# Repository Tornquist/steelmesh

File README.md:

# Steelmesh
(Twitch Plays ECE477 -- Collaborative Robot Project)

This repository is set up to simulate an organization.  Instead of a seperate repository for each piece of the project, each branch represents a valid section/piece of the project.

## irc_work
The irc bot and rails webserver that manages the stream of communication from Twitch.TV and allows the robots to request commands. 

## WiFi
The final embedded robot software.

## PCB
The PCB design used for the robots

## raspberry_pi
The logic that controlled the scoring system and webcam feeds that ran the arena.

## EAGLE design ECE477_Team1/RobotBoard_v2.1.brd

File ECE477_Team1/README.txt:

1)  Install Eagle
2)  Add the Sparkfun libraries (https://learn.sparkfun.com/tutorials/how-to-install-and-setup-eagle/using-the-sparkfun-libraries)
3)  Copy the microchip.lbr file into your lbr directory (it will overwrite the current microchip library).
3.1)  Also copy the Johanson_antenna.lbr and crw.lbr files
4)  You probably have to add the project folder to the "Projects" directory list (kinda like the libraries).
5)  Open the schematic/board and look at it and stuff.
6)  ????????????
7)  Profit.

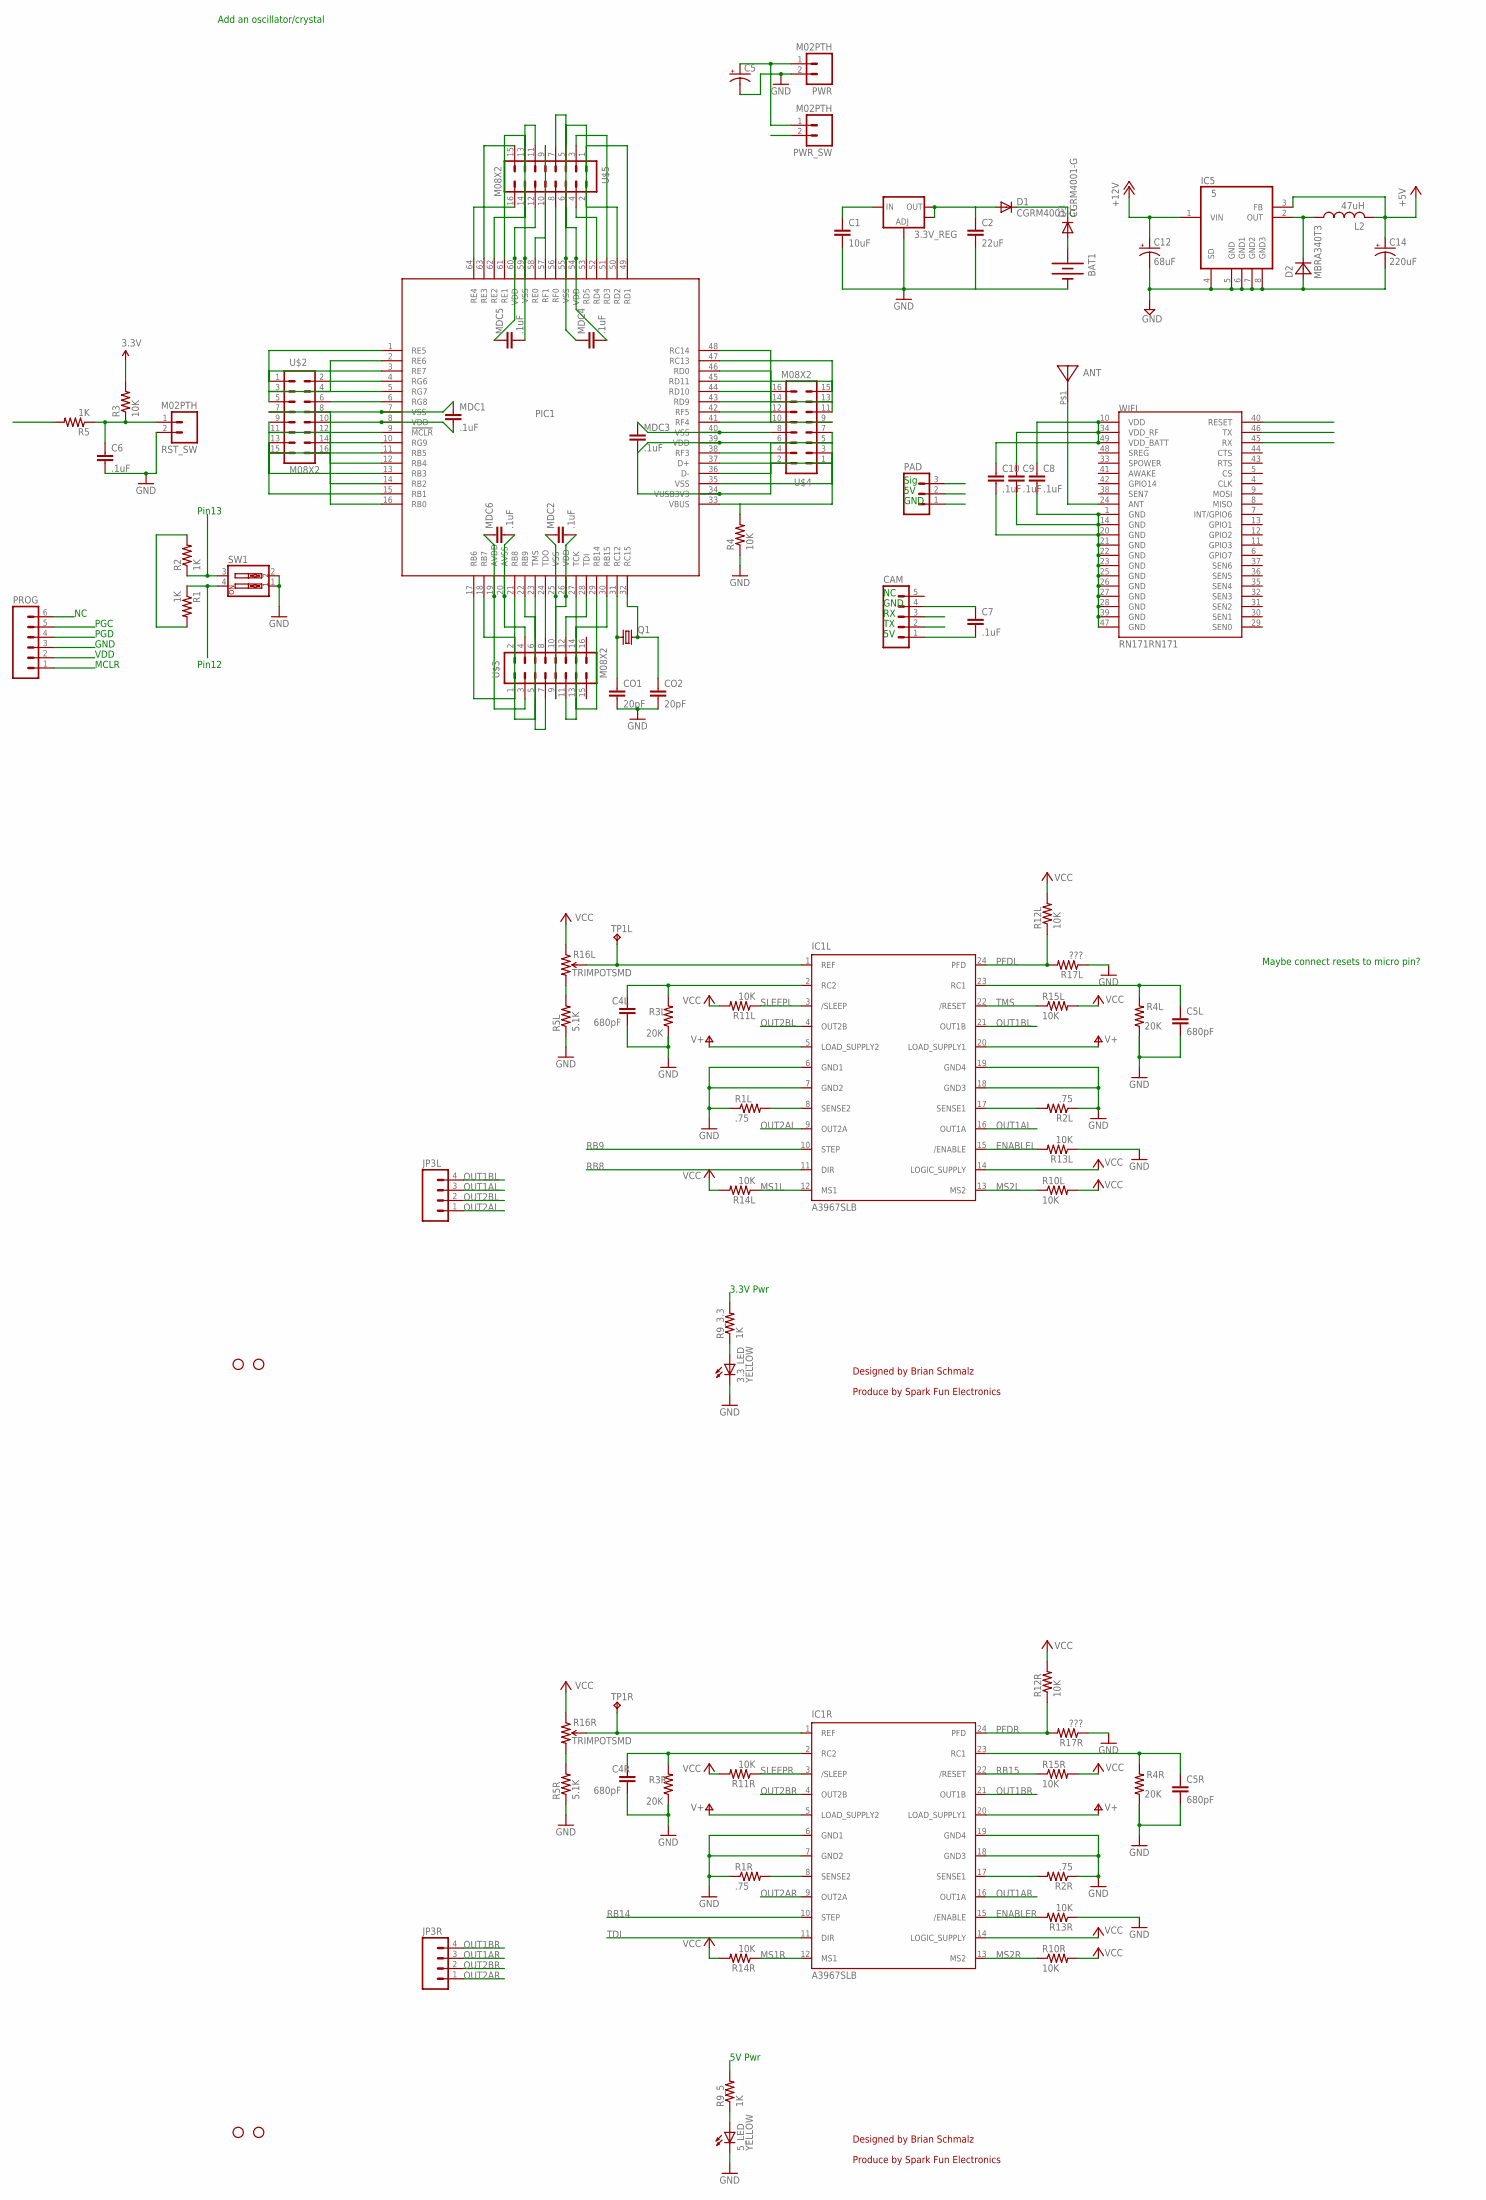
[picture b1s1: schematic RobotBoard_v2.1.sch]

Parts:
3.3V_REG: V_REG_LM1117SOT223; SOT223
3.3_LED, 5_LED: YELLOW; LED-0603
ANT: 2450AT18A100
BAT1: BATTERY20PTH; BATTCOM_20MM_PTH
C1: 10uF; 0603
C2: 22uF; 0603
C4L, C4R, C5L, C5R: 680pF; C0402
C5: CAP_POLPTH4; CPOL-RADIAL-1000UF-25V
C6, C7, C8, C9, C10: .1uF; 0603
C12: 68uF; PANASONIC_D
C14: 220uF; PANASONIC_D
CAM: M05LOCK; 1X05_LOCK
CO1, CO2: 20pF; 0603
D1, D3: CGRM4001-G; SOD-123_MINI-SMA
D2: MBRA340T3; SMA
IC1L, IC1R: A3967SLB; SO24W
IC5: 5; SO08
JP1, JP2, JP8, JP9: STAND-OFF
JP3L, JP3R: M041X04_NO_SILK; 1X04_NO_SILK
L2: 47uH; 6000-XXXX-RC
MDC1, MDC2, MDC3, MDC4, MDC5, MDC6: .1uF; 0603
PAD: M03POLAR; MOLEX-1X3
PIC1: PIC32MZ2048ECM064; TQFP64-10X10X1MM
PROG: M06LOCK; 1X06_LOCK
PWR: M02PTH; 1X02
PWR_SW: M02PTH; 1X02
Q1: CRYSTALHC49UP; HC49UP
R1, R2, R5, R9_3.3, R9_5: 1K; C0402
R1L, R1R, R2L, R2R: .75; R0805
R3, R4, R10L, R10R, R11L, R11R, R12L, R12R, R13L, R13R, R14L, R14R, R15L, R15R: 10K; C0402
R3L, R3R, R4L, R4R: 20K; C0402
R5L, R5R: 5.1K; C0402
R16L, R16R: TRIMPOTSMD; TRIMPOT-3MM
R17L, R17R: ???; C0402
RST_SW: M02PTH; 1X02
SW1: SW_DIP-2; DIPSWITCH-02
TP1L, TP1R: TPPAD1-13; P1-13
U$2, U$3, U$4, U$5: M08X2; 2X8
WIFI: RN171RN171; RN171

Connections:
3.3V: C8.1, C9.1, C10.1, D1.C, D3.C, IC1L.14 (LOGIC_SUPPLY), IC1R.14 (LOGIC_SUPPLY), MDC1.2, MDC2.2, MDC3.2, MDC4.2, MDC5.1, MDC6.1, PIC1.8 (VDD), PIC1.19 (AVDD), PIC1.26 (VDD), PIC1.34 (VUSB3V3), PIC1.39 (VDD), PIC1.54 (VDD), PIC1.60 (VDD), PROG.2, R1.2, R2.2, R3.2, R9_3.3.2, R10L.2, R10R.2, R11L.2, R11R.2, R12L.2, R12R.2, R14L.2, R14R.2, R15L.2, R15R.2, R16L.1 (CCW), R16R.1 (CCW), U$2.8, U$3.3, U$3.10, U$4.2, U$4.7, U$5.6, U$5.12, WIFI.10 (VDD), WIFI.34 (VDD_RF), WIFI.49 (VDD_BATT)
5V: 3.3V_REG.3 (IN), C1.1, C7.2, C14.+, CAM.1, IC5.3 (FB), L2.2, PAD.2, R9_5.2
12V: C12.+, IC1L.5 (LOAD_SUPPLY2), IC1L.20 (LOAD_SUPPLY1), IC1R.5 (LOAD_SUPPLY2), IC1R.20 (LOAD_SUPPLY1), IC5.1 (VIN), PWR_SW.2
!MCLR: PIC1.9 (!MCLR), PROG.1, R5.2, U$2.9
A44: C6.1, R3.1, R5.1, RST_SW.1
D+: PIC1.37 (D+), U$4.5
D-: PIC1.36 (D-), U$4.4
ENABLEL: IC1L.15 (/ENABLE), R13L.2
ENABLER: IC1R.15 (/ENABLE), R13R.2
GND: 3.3V_REG.1 (ADJ), 3.3_LED.C, 5_LED.C, BAT1.2 (-), C1.2, C2.2, C4L.2, C4R.2, C5.2 (-), C5L.2, C5R.2, C6.2, C7.1, C8.2, C9.2, C10.2, C12.-, C14.-, CAM.4, CO1.2, CO2.2, D2.A, IC1L.6 (GND1), IC1L.7 (GND2), IC1L.18 (GND3), IC1L.19 (GND4), IC1R.6 (GND1), IC1R.7 (GND2), IC1R.18 (GND3), IC1R.19 (GND4), IC5.4 (SD), IC5.5 (GND), IC5.6 (GND1), IC5.7 (GND2), IC5.8 (GND3), MDC1.1, MDC2.1, MDC3.1, MDC4.1, MDC5.2, MDC6.2, PAD.1, PIC1.7 (VSS), PIC1.20 (AVSS), PIC1.25 (VSS), PIC1.35 (VSS), PIC1.40 (VSS), PIC1.55 (VSS), PIC1.59 (VSS), PROG.3, PWR.2, R1L.1, R1R.1, R2L.1, R2R.1, R3L.1, R3R.1, R4.1, R4L.1, R4R.1, R5L.1, R5R.1, R13L.1, R13R.1, R17L.1, R17R.1, RST_SW.2, SW1.1, SW1.2, U$2.7, U$3.4, U$3.9, U$4.3, U$4.8, U$5.7, U$5.11, WIFI.1 (GND), WIFI.14 (GND), WIFI.20 (GND), WIFI.21 (GND), WIFI.22 (GND), WIFI.23 (GND), WIFI.25 (GND), WIFI.26 (GND), WIFI.27 (GND), WIFI.28 (GND), WIFI.39 (GND), WIFI.47 (GND)
MS1L: IC1L.12 (MS1), R14L.1
MS1R: IC1R.12 (MS1), R14R.1
MS2L: IC1L.13 (MS2), R10L.1
MS2R: IC1R.13 (MS2), R10R.1
unnamed: IC1L.8 (SENSE2), R1L.2
unnamed: 3.3_LED.A, R9_3.3.1
unnamed: IC1L.17 (SENSE1), R2L.2
unnamed: BAT1.1 (+), D3.A
unnamed: C4L.1, IC1L.2 (RC2), R3L.2
unnamed: CO1.1, PIC1.31 (RC12), Q1.1
unnamed: C5L.1, IC1L.23 (RC1), R4L.2
unnamed: IC1R.8 (SENSE2), R1R.2
unnamed: IC1R.17 (SENSE1), R2R.2
unnamed: C4R.1, IC1R.2 (RC2), R3R.2
unnamed: R5L.2, R16L.3 (CW)
unnamed: IC1L.1 (REF), R16L.2 (WIPER), TP1L.1
unnamed: C5R.1, IC1R.23 (RC1), R4R.2
unnamed: IC1R.1 (REF), R16R.2 (WIPER), TP1R.1
unnamed: CO2.1, PIC1.32 (RC15), Q1.2
unnamed: R5R.2, R16R.3 (CW)
unnamed: 5_LED.A, R9_5.1
unnamed: ANT.P$1, WIFI.24 (ANT)
unnamed: C5.1 (+), PWR.1, PWR_SW.1
unnamed: D2.C, IC5.2 (OUT), L2.1
OUT1AL: IC1L.16 (OUT1A), JP3L.3
OUT1AR: IC1R.16 (OUT1A), JP3R.3
OUT1BL: IC1L.21 (OUT1B), JP3L.4
OUT1BR: IC1R.21 (OUT1B), JP3R.4
OUT2AL: IC1L.9 (OUT2A), JP3L.1
OUT2AR: IC1R.9 (OUT2A), JP3R.1
OUT2BL: IC1L.4 (OUT2B), JP3L.2
OUT2BR: IC1R.4 (OUT2B), JP3R.2
PFDL: IC1L.24 (PFD), R12L.1, R17L.2
PFDR: IC1R.24 (PFD), R12R.1, R17R.2
RB0: PIC1.16 (RB0), PROG.4, U$2.16
RB1: PIC1.15 (RB1), PROG.5, U$2.15
RB2: PIC1.14 (RB2), U$2.14
RB3: PIC1.13 (RB3), R2.1, SW1.3, U$2.13
RB4: PIC1.12 (RB4), R1.1, SW1.4, U$2.12
RB5: PIC1.11 (RB5), U$2.11
RB6: PIC1.17 (RB6), U$3.1
RB7: PIC1.18 (RB7), U$3.2
RB8: IC1L.11 (DIR), PIC1.21 (RB8), U$3.5
RB9: IC1L.10 (STEP), PIC1.22 (RB9), U$3.6
RB14: IC1R.10 (STEP), PIC1.29 (RB14), U$3.13
RB15: IC1R.22 (/RESET), PIC1.30 (RB15), R15R.1, U$3.14
RC13: PIC1.47 (RC13), U$4.15
RC14: PIC1.48 (RC14), U$4.16
RD0: CAM.3, PIC1.46 (RD0), U$4.14
RD1: PIC1.49 (RD1), U$5.1
RD2: PIC1.50 (RD2), U$5.2
RD3: PIC1.51 (RD3), U$5.3
RD4: PIC1.52 (RD4), U$5.4
RD5: PIC1.53 (RD5), U$5.5
RD9: CAM.2, PIC1.43 (RD9), U$4.11
RD10: PIC1.44 (RD10), U$4.12
RD11: PIC1.45 (RD11), U$4.13
RE0: PIC1.58 (RE0), U$5.10
RE1: PIC1.61 (RE1), U$5.13
RE2: PIC1.62 (RE2), U$5.14
RE3: PIC1.63 (RE3), U$5.15
RE4: PIC1.64 (RE4), U$5.16
RE5: PIC1.1 (RE5), U$2.1
RE6: PIC1.2 (RE6), U$2.2
RE7: PIC1.3 (RE7), U$2.3
RF0: PIC1.56 (RF0), U$5.8
RF1: PIC1.57 (RF1), U$5.9
RF3: PAD.3, PIC1.38 (RF3), U$4.6
RF4: PIC1.41 (RF4), U$4.9
RF5: PIC1.42 (RF5), U$4.10
RG6: PIC1.4 (RG6), U$2.4, WIFI.40 (RESET)
RG7: PIC1.5 (RG7), U$2.5, WIFI.45 (RX)
RG8: PIC1.6 (RG8), U$2.6, WIFI.46 (TX)
RG9: PIC1.10 (RG9), U$2.10
SKSDJIOJ: 3.3V_REG.2 (OUT), 3.3V_REG.4 (OUT), C2.1, D1.A
SLEEPL: IC1L.3 (/SLEEP), R11L.1
SLEEPR: IC1R.3 (/SLEEP), R11R.1
TCK: PIC1.27 (TCK), U$3.11
TDD: PIC1.24 (TDO), U$3.8
TDI: IC1R.11 (DIR), PIC1.28 (TDI), U$3.12
TMS: IC1L.22 (/RESET), PIC1.23 (TMS), R15L.1, U$3.7
VBUS: PIC1.33 (VBUS), R4.2, U$4.1

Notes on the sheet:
Designed by Brian Schmalz
Produce by Spark Fun Electronics
Add an oscillator/crystal
GND
Sig
Maybe connect resets to micro pin?
5V Pwr
3.3V Pwr
MCLR
VDD
PGD
PGC
Pin12
Pin13

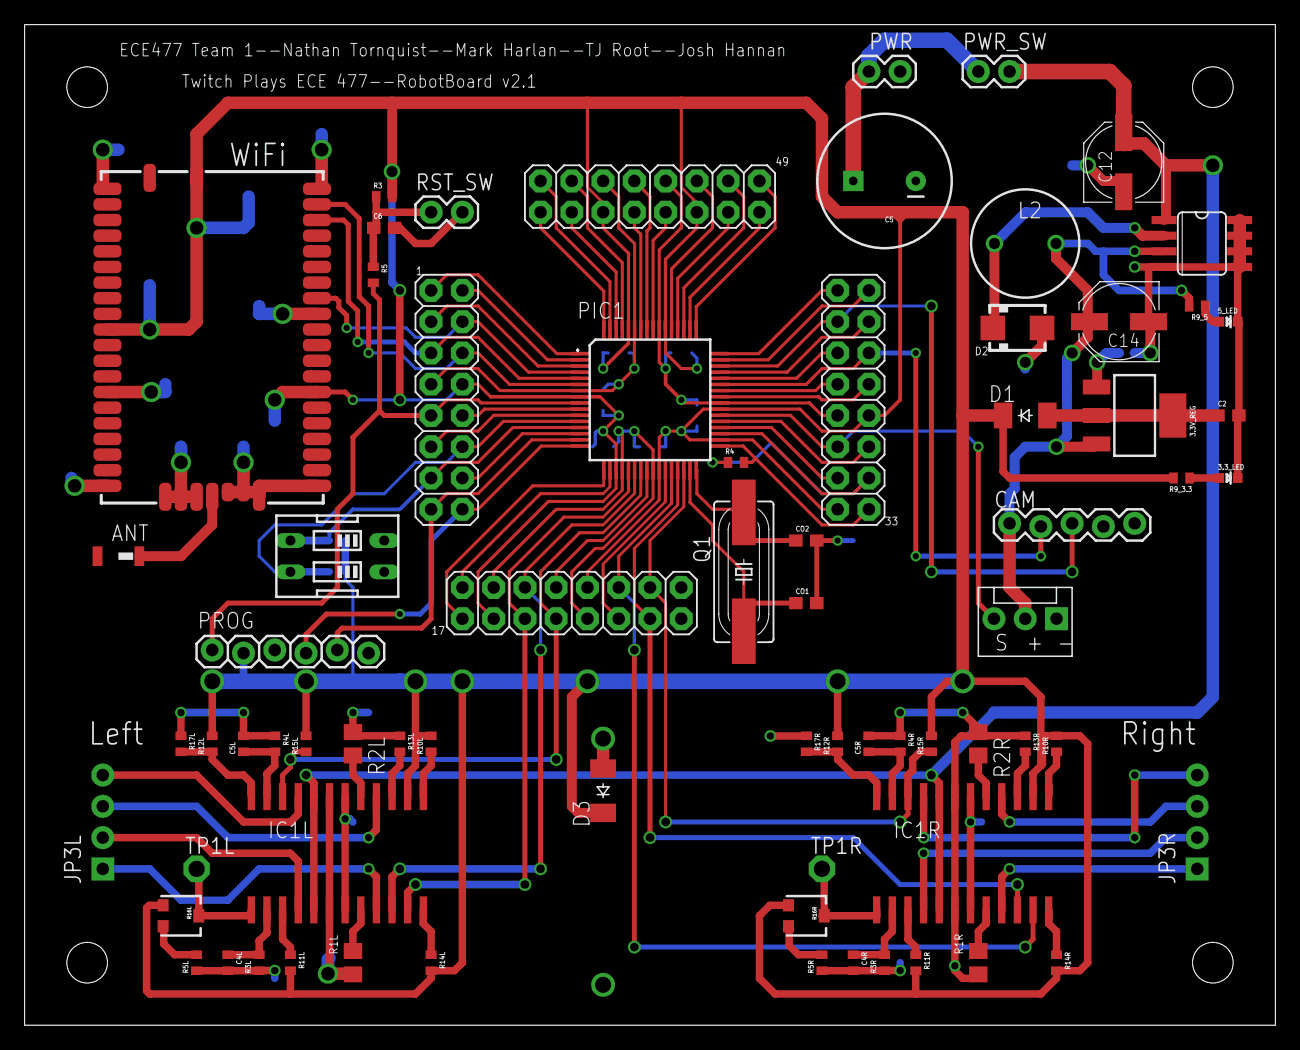
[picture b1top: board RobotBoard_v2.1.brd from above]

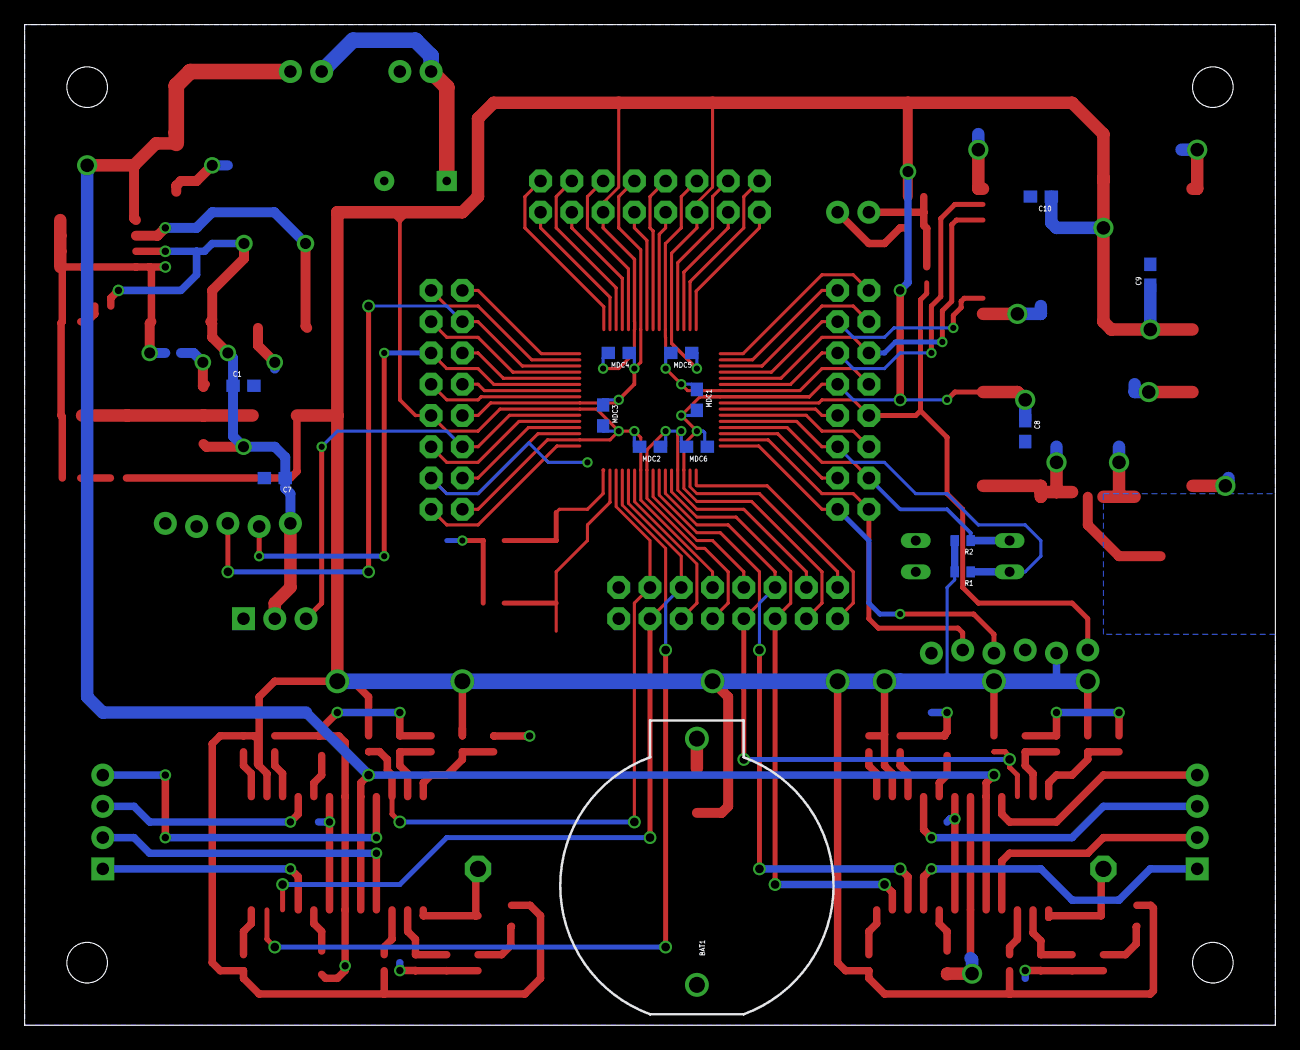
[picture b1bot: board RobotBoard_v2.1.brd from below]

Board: 2 copper layers, 101.6 x 81.3 mm, 89 parts (14 on the bottom side), 92 nets.

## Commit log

2015-01-31 Added rasberry pi scripts to git
2015-02-01 Basic research, cinch is the right gem to use
2015-02-03 Working cinch bot with twitch stream
2015-02-10 webserver with redis integration, works for one channel. Made bot a rake task
2015-02-26 Project skeleton commit
    Setup basic file structure without content. Set configuration variables
    and pin-outs according to updated README.
2015-02-26 Added code to wake camera
    Code is untested, but serves as a good example of my planned approach.
2015-02-27 Initial commit of PCB files (v1.0)
2015-02-27 Added Antenna
2015-02-28 Working score endpoints
2015-03-01 Updated Power Regulators and created v2.0
2015-03-02 Finished first draft of full camera code (untested)
    All code is written to wake the camera, initialize it, and receive an
    image. This includes the state machine. It hasn't been tested on the
    camera hardware yet.
2015-03-09 Communication for Wifi Module working
    Able to send put the WiFi Module in command mode and receive the
    response.
2015-03-10 Receiving files through web requests
2015-03-11 Added Version 2.1
2015-03-13 Added Battery
2015-03-21 added mjpg options and motion options, mjpg is faster
2015-03-21 Working webcam scripts
2015-03-21 added startup script to git
2015-03-21 Added webcam feed
2015-03-22 UART Working
    UART is working correctly. Able to transmit and receive strings without
    Harmony. Still working on WiFi command syntax.
2015-03-22 WiFi Configuration Up
    We can now configure the WiFi module however we want
2015-03-23 WiFi Configuration Complete
    Finished working out bugs in wifi config. Changed syntax of commands
    and separated functions into multiple files.
2015-03-25 Command system adapted to work with requests for commands
2015-03-25 Added commands controler
2015-03-26 PWM Working and New File Organization
    basic PWM functionality is operational. I also reorganized the files to
    separate the logic for the UART, WiFi module, and motors.
2015-03-27 Current status of WiFi and UART logic
2015-03-29 First semi-functional draft of register version
    Inconsistently receives responses from the camera up until the DATA
    command, which receives NULL values and causes it to fail.
2015-04-03 Some stuff with interrupts
    Doesn't work correctly, but some of it might still be useful so I'm
    pushing it.
2015-04-03 Commit so I can switch to micro
2015-04-03 Pulled some camera logic to just test uart, it looks like the interrupt is not being triggered on receive correctly.
    When connected to a Raspberry Pi, the uart triggered on a send, when TX
    and RX were connected on the board, the interrupt was never triggered
2015-04-07 communication
    yes
2015-04-08 Receiving commands
    YAASS
2015-04-08 receiving multiple commands
    yeah boi
2015-04-08 Working irc_bot and command system to actually send commands to the robot. With the successful setup of wifi, this is working
2015-04-08 wifi
    k
2015-04-08 motors and wifi communication
    yay
2015-04-11 added reset button and second team scoring button
2015-04-11 code organization
2015-04-13 nothing
    i did nothing
2015-04-13 Movement
2015-04-13 Robot moves forward at a good pace!
    Used "make and program device" to get the robot to move forward on its
    own.
2015-04-13 HE KICKS
2015-04-14 Robot Movement functions
2015-04-14 Cleaned up motor control logic, and added global delay function
2015-04-14 Removed old unused projects from git
2015-04-14 Read and set device id from input DIP switches
    I did it quickly and it's destructive reading. It sets all of B to
    input, then all back to output. If you ever needed to change it so that
    you would have input continuously on other pins, this code would be a
    significant problem.
2015-04-15 Added reset options
2015-04-15 update
    cleaned up some of the code
2015-04-17 Code works sporadically when it does, it communicates fully
2015-04-20 Working completely on robot 2

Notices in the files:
ECE477_Team1/RobotBoard_v2.1.sch:
licensed under a Creative Commons
Copyright 2012
parts and their libraries:
SparkFun-Connectors: Licensing: CC v3.0 Share-Alike You are welcome to use this library for commercial purposes.
SparkFun-PowerIC: Licensing: Creative Commons ShareAlike 4.0 International - https://creativecommons.org/licenses/by-sa/4.0
